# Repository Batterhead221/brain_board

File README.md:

# BRAIN_BOARD

Custom STM32H753 main controller board for modular motion, control, storage, communication, and daughter-board expansion.

BRAIN_BOARD is the clean logic/control board in a modular hardware system. It handles MCU control, communication, debugging/programming, storage, sensor inputs, and daughter-board interfaces. Noisy motor power and phase switching are kept on external boards such as DIRTY_MTR_BOARD.

## Project Status

In progress. Main controller schematic and PCB layout under development/review.

## System Role

```text
Host / USB / RS485 / CAN
        ↓
BRAIN_BOARD
        ↓ STEP / DIR / SPI / GPIO
DIRTY_MTR_BOARD / daughter boards
        ↓
Motor / sensors / external hardware
```

BRAIN_BOARD does not directly drive stepper motor coils. Motor current, switching, and noisy power handling belong on dedicated daughter boards.

## Key Specs

| Item | Value |
|---|---|
| MCU | STM32H753ZITx |
| Package | LQFP-144 |
| Logic rail | +3.3V |
| USB | USB-C |
| External communication | RS485, CAN |
| Storage | microSD |
| Nonvolatile memory | SPI FRAM |
| Debug/programming | SWD / debug UART headers |
| Daughter-board support | Motor/control, analog I/O, manual jog, external flags |
| Power options | USB or VIN path with jumper selection |
| Board role | Main controller / system brain |

## Main Features

- STM32H753 main MCU
- USB-C connector for USB data/power path
- USB VBUS fused input
- VIN input path
- Jumper-selectable power source
- +3.3V regulation and local decoupling
- RS485 transceiver interface
- CAN interface connector
- SPI FRAM
- microSD card interface
- SWD programming/debug header
- Debug UART header
- User switch
- Boot button
- Reset button
- Status LEDs
- Analog input header
- Daughter-board connectors
- Motor-control signals routed to external motor driver board
- Active-low home/crash/manual-jog style inputs
- Labeled test points and silkscreen notes

## Power Architecture

BRAIN_BOARD is intended to keep logic power clean and separate from noisy motor power.

```text
USB-C / VIN input path
        ↓
power selection / protection
        ↓
+3.3V logic rail
        ↓
STM32H753 + memory + communication interfaces
```

Motor power is not generated or switched directly on BRAIN_BOARD.

## Daughter-Board Strategy

Planned or related daughter boards include:

- DIRTY_MTR_BOARD for motor driving and noisy power handling
- DUMB_MANUAL_MTR_BOARD for external manual jog buttons
- Sensor / analog input boards
- Communication or debug helper boards

Manual jog style inputs are intended to be active-low. External buttons pull the signal to GND when pressed.

## PCB Notes

Design priorities:

- Keep MCU decoupling tight and local
- Keep the ground system solid and low impedance
- Route communication interfaces cleanly
- Keep noisy motor-driver current off the main controller board
- Use clear connector labels and test points
- Preserve clean SWD/debug access

## Repository Output Images

Expected image paths for GitHub README rendering:

```text
Outputs/
  IMG/
    3D-T.png
    3D-B.png
    SCHEMATIC.png
    L1-SIG.png
    L2-3V3.png
    L3-GND.png
    L4-MIX.png
```

## Safety / Design Note

BRAIN_BOARD is a low-voltage controller PCB. Motor power, external loads, and high-current switching should be handled on separate boards with appropriate power routing, protection, and review.

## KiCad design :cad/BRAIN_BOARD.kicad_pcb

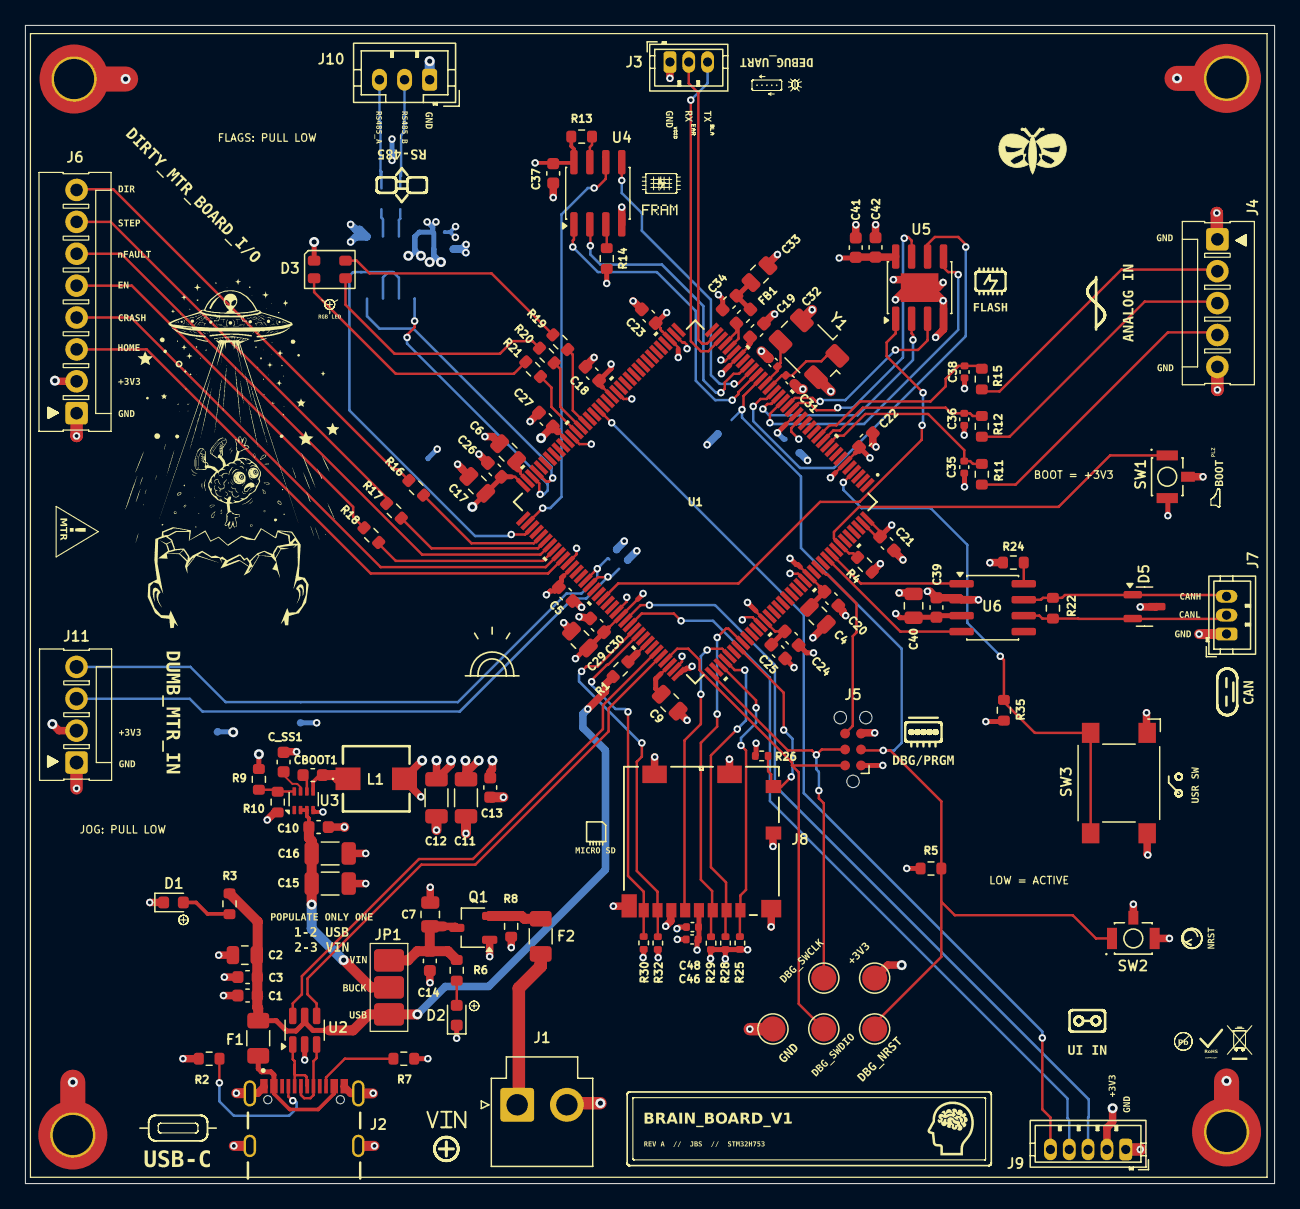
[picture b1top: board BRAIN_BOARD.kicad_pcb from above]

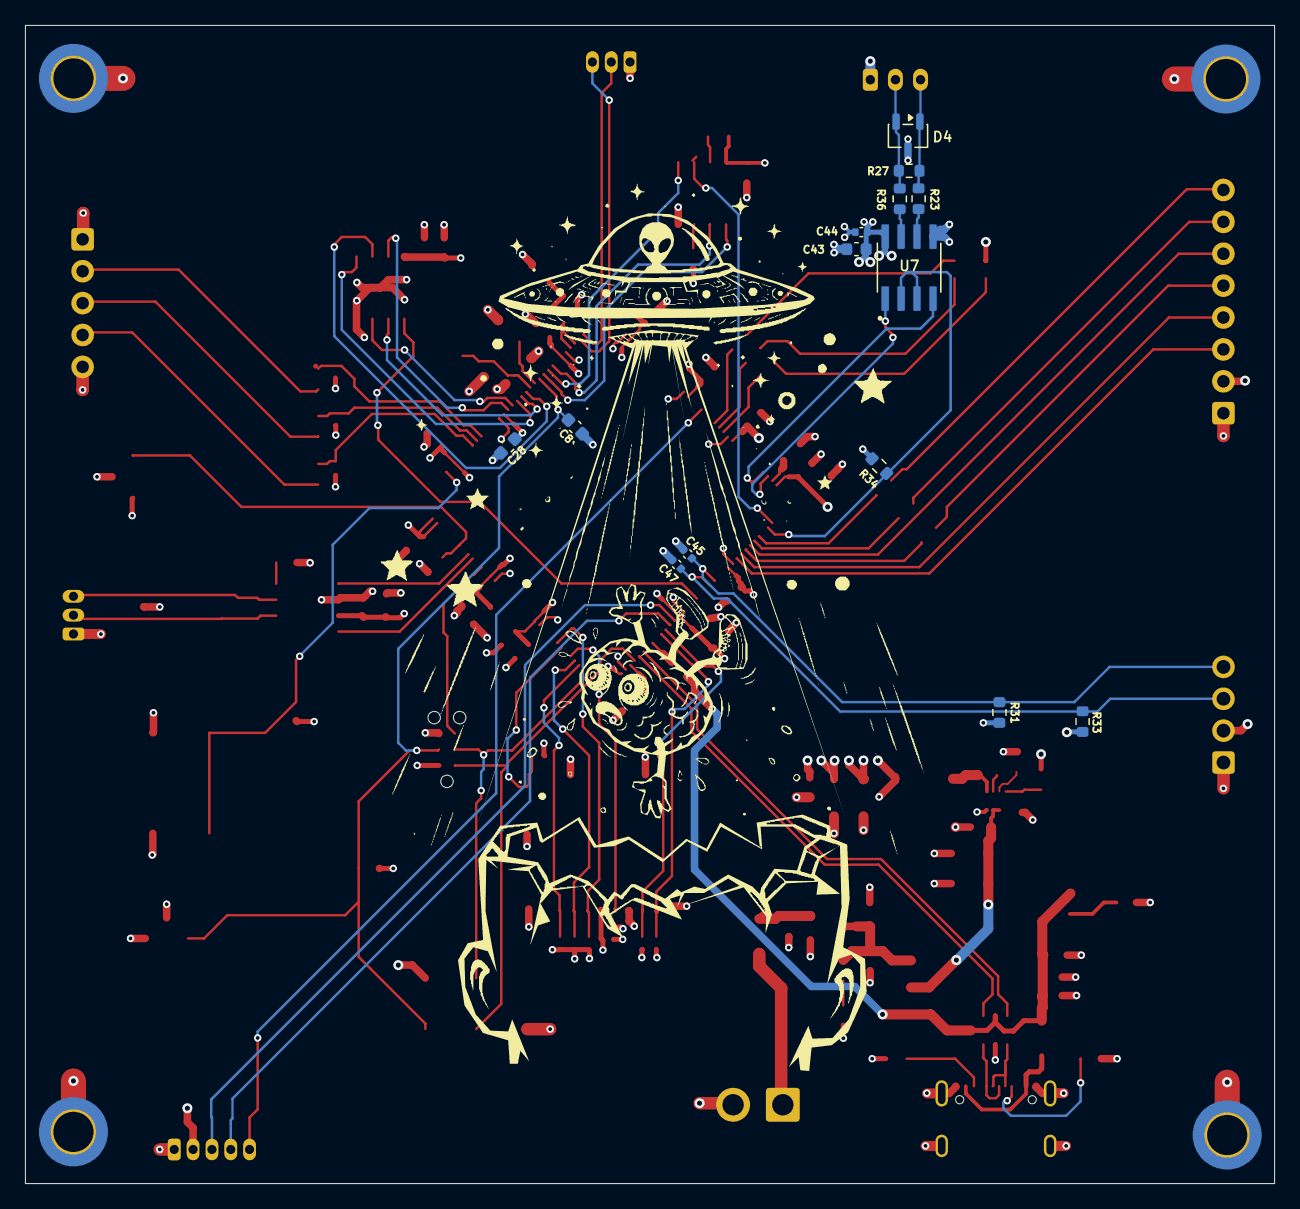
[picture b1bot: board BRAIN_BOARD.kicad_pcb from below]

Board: 4 copper layers, 99.5 x 92.2 mm, 128 parts (14 on the bottom side), 92 nets.

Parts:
C1, C5, C8, C10, C13, C14, C18, C19, C20, C21, C22, C23, C24, C25, C26, C27, C28, C30, C34, C37, C41: 100nF; C_0603_1608Metric
C2, C7: 10µF; C_0805_2012Metric
C3, C42: 1µF; C_0603_1608Metric
C4, C6, C9: 2.2µF; C_0805_2012Metric
C11, C12: 22µF; C_1206_3216Metric
C15, C16: 10µF; C_1206_3216Metric
C17, C40: 4.7µF; C_0805_2012Metric
C29, C33: 1µF; C_0805_2012Metric
C31, C32: 18pF; C_0402_1005Metric
C35, C36, C38, C45, C47: 10nF; C_0402_1005Metric
C39: 100NF; C_0603_1608Metric
C43: 10µF; C_0603_1608Metric
C44, C46: 100nF; C_0402_1005Metric
C48: 1µF; C_0402_1005Metric
CBOOT1: 100nF; C_0603_1608Metric
C_SS1: 33nF; C_0603_1608Metric
D1: +5V_SIG; LED_0603_1608Metric
D2: LED_GREEN; LED_0603_1608Metric
D3: CLV1L-FKB; LED_Cree-PLCC4_3.2x2.8mm_CCW
D4: SM712_SOT23; SOT-23-3
D5: SM24CANB-02HTG (SOT-23-3); SOT-23
F1, F2: 1206; Fuse_1206_3216Metric
FB1: FERRITE_BEAD; Fuse_0603_1608Metric
H1, H2, H3, H4: MountingHole_Pad; MountingHole_3.2mm_M3_ISO14580_Pad_TopBottom
J1: VH; JST_VH_B2P-VH_1x02_P3.96mm_Vertical
J2: USB4105-GF-A (USB-C); GCT_USB4105-GF-A
J3, J7: ZH-3; JST_ZH_B3B-ZR_1x03_P1.50mm_Vertical
J4: MTA-5
J5: TC2030-NL; Tag-Connect_TC2030-IDC-NL_2x03_P1.27mm_Vertical
J6: MTA-8
J8: 1040310811; 104031-0811_MOL
J9: ZH-5; JST_ZH_B5B-ZR_1x05_P1.50mm_Vertical
J10: PH-3; JST_PH_B3B-PH-K_1x03_P2.00mm_Vertical
J11: 640454-4; MTA-4
JP1: BEEFY_JUMPER; PWR_JMP_BEEFY
L1: 4.7µH; L_SRP5030TA4R7M
Q1: AO3407A (SOT-23-3); TSOT-23
R1, R5, R8, R10, R13, R14, R31, R33, R34, R35: 10K; R_0603
R2, R7: 5.1K; R_0603
R3, R6: 750; R_0603
R4: 5K1; R_0603
R9: 31.6K; R_0603
R11, R12, R15, R16, R17, R18: 100; R_0603
R19, R20, R21: 470; R_0603
R22, R27: 120; R_0603
R23, R36: 0; R_0603
R24: 4.7K; R_0603
R25, R28, R29, R30, R32: 47K; R_0402_1005Metric
R26: 10K; R_0402_1005Metric
SW1, SW2: B3U-1100P; SW_B3U-1100P
SW3: SW_SPST_Omron_B3FS-100xP
TP1: 3.3V; TestPoint_Pad_D2.0mm
TP2: GND; TestPoint_Pad_D2.0mm
TP3: DBG_SWDIO; TestPoint_Pad_D2.0mm
TP4: DBG_NRST; TestPoint_Pad_D2.0mm
TP5: DBG_SWCLK; TestPoint_Pad_D2.0mm
U1: LQFP-144; LQFP144-20x20mm
U2: USBLC6-2SC6_(SOT-23-6); SOT-23-6
U3: TPS62933DRLR; SOT-583-8
U4: FM25V20A-G_(SOIC-8); SOIC-8_3.9x4.9mm_P1.27mm
U5: W25Q128JVEIM_TR; SOIC-8-1EP_3.9x4.9mm_P1.27mm_EP2.29x3mm
U6: TJA1051T/3_(SOIC-8); SOIC-8_3.9x4.9mm_P1.27mm
U7: THVD1450DR; SOIC127P599X175-8N
Y1: ABM3B-8.000MHZ-B2-T; Crystal_SMD_Abracon_ABM3B-4Pin_5.0x3.2mm

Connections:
+3.3V: C4.1, C5.1, C11.2, C12.2, C13.1, C17.1, C18.1, C19.1, C20.1, C21.1, C22.1, C23.1, C24.1, C25.1, C26.1, C27.1, C28.1, C29.2, C30.2, C37.2, C39.2, C40.2, C41.2, C42.2, C43.1, C44.2, C46.1, C48.2, D3.1 (A), J5.1 (+3V3), J6.2, J8.4 (VDD), J9.2, J11.2, L1.2, R5.1, R9.2, R13.1, R14.2, R25.2, R26.1, R28.2, R29.2, R30.1, R31.1, R32.1, R33.1, R35.2, SW1.2, TP1.1, U1.6 (VBAT), U1.17 (VDD), U1.30 (VDD), U1.39 (VDD), U1.52 (VDD), U1.62 (VDD), U1.72 (VDD), U1.84 (VDD), U1.95 (VDD33USB), U1.108 (VDD), U1.121 (VDD), U1.131 (VDD), U1.143 (PDR_ON), U1.144 (VDD), U4.8 (VDD), U5.8 (VCC), U6.3 (VCC), U7.8 (VCC)
/BRAIN_BOARD/+3V3_A: FB1.2, U1.32 (VREF+), U1.33 (VDDA)
/BRAIN_BOARD/+5V_SIG: D1.2 (A), R3.2
/BRAIN_BOARD/+12V: F2.1, J1.1
/BRAIN_BOARD/+12V_SIG: D2.2 (A), R6.2
/BRAIN_BOARD/ADC_5V_SENSE: C38.1, R15.1, U1.12 (PF2)
/BRAIN_BOARD/ADC_5V_SENSE_RAW: J4.2, R15.2
/BRAIN_BOARD/ADC_24V_SENSE: C36.1, R12.1, U1.11 (PF1)
/BRAIN_BOARD/ADC_24V_SENSE_RAW: J4.3, R12.2
/BRAIN_BOARD/ADC_CURRENT_SENSE: C35.1, R11.1, U1.10 (PF0)
/BRAIN_BOARD/ADC_CURRENT_SENSE_RAW: J4.4, R11.2
/BRAIN_BOARD/BOOT0: R4.1, SW1.1, U1.138 (BOOT0)
/BRAIN_BOARD/B_LED: R19.1, U1.58 (PE7)
/BRAIN_BOARD/CAN2_RX: U1.135 (PB5), U6.4 (RXD)
/BRAIN_BOARD/CAN2_TX: U1.136 (PB6), U6.1 (TXD)
/BRAIN_BOARD/CAN_HI: D5.1 (PIN_1), J7.3, R22.1, U6.7 (CANH)
/BRAIN_BOARD/CAN_LO: D5.2 (PIN_2), J7.2, R22.2, U6.6 (CANL)
/BRAIN_BOARD/CRASH_FLAG: J6.4, U1.81 (PD12)
/BRAIN_BOARD/D+: J2.A6 (D+), J2.B6 (D+), U2.3 (L2)
/BRAIN_BOARD/D-: J2.A7 (D-), J2.B7 (D-), U2.1 (L1)
/BRAIN_BOARD/DBG_NRST: C8.2, J5.3 (NRST), R5.2, SW2.1, TP4.1, U1.25 (NRST)
/BRAIN_BOARD/DBG_SWCLK: J5.4 (SWCLK), TP5.1, U1.109 (PA14)
/BRAIN_BOARD/DBG_SWDIO: J5.2 (SWDIO), TP3.1, U1.105 (PA13)
/BRAIN_BOARD/DBG_SWO: J5.6 (SWO), U1.133 (PB3)
/BRAIN_BOARD/DIR: R16.1, U1.77 (PD8)
/BRAIN_BOARD/ENABLE: R18.1, U1.80 (PD11)
/BRAIN_BOARD/FRAM_CS: U1.26 (PC0), U4.1 (~CS)
/BRAIN_BOARD/FRAM_MISO: U1.28 (PC2_C), U4.2 (SO)
/BRAIN_BOARD/FRAM_MOSI: U1.27 (PC1), U4.5 (SI)
/BRAIN_BOARD/FRAM_SCK: U1.74 (PB13), U4.6 (SCK)
/BRAIN_BOARD/G_LED: R20.1, U1.59 (PE8)
/BRAIN_BOARD/HOME_FLAG: J6.3, U1.82 (PD13)
/BRAIN_BOARD/HSE_IN: C31.1, U1.23 (PH0-OSC_IN), Y1.1
/BRAIN_BOARD/HSE_OUT: C32.2, U1.24 (PH1-OSC_OUT), Y1.3
/BRAIN_BOARD/JOG_FWD: C45.1, J11.4, R31.2, U1.87 (PG2)
/BRAIN_BOARD/JOG_REV: C47.1, J11.3, R33.2, U1.88 (PG3)
/BRAIN_BOARD/QSPI_CLK: U1.22 (PF10), U5.6 (CLK)
/BRAIN_BOARD/QSPI_CS: U1.91 (PG6), U5.1 (~CS)
/BRAIN_BOARD/QSPI_IO0: U1.20 (PF8), U5.5 (DI_(IO0))
/BRAIN_BOARD/QSPI_IO1: U1.21 (PF9), U5.2 (DO_(IO1))
/BRAIN_BOARD/QSPI_IO2: U1.19 (PF7), U5.3 (~WP_(IO2))
/BRAIN_BOARD/QSPI_IO3: U1.18 (PF6), U5.7 (~HOLD_OR_/RESET_(IO3))
/BRAIN_BOARD/RS485_A: D4.1 (A1), J10.3, R23.2, R27.1
/BRAIN_BOARD/RS485_B: D4.2 (A2), J10.2, R27.2, R36.2
/BRAIN_BOARD/RS485_DE: R34.1, U1.75 (PB14), U7.2 (~RE), U7.3 (DE)
/BRAIN_BOARD/RS485_RX: U1.70 (PB11), U7.1 (RO)
/BRAIN_BOARD/RS485_TX: U1.69 (PB10), U7.4 (DI)
/BRAIN_BOARD/R_LED: R21.1, U1.60 (PE9)
/BRAIN_BOARD/SD_ CD: J8.10 (SW_DETECT), R26.2, U1.115 (PD1)
/BRAIN_BOARD/SD_CLK: J8.5 (CLK), U1.113 (PC12)
/BRAIN_BOARD/SD_CMD: J8.3 (CMD), R29.1, U1.116 (PD2)
/BRAIN_BOARD/SD_D0: J8.7 (DAT0), R32.2, U1.98 (PC8)
/BRAIN_BOARD/SD_D1: J8.8 (DAT1), R30.2, U1.99 (PC9)
/BRAIN_BOARD/SD_D2: J8.1 (DAT2), R25.1, U1.111 (PC10)
/BRAIN_BOARD/SD_D3: J8.2 (CD/DAT3), R28.1, U1.112 (PC11)
/BRAIN_BOARD/STEP: R17.1, U1.78 (PD9)
/BRAIN_BOARD/UART_DBG_RX: J3.2, U1.35 (PA1)
/BRAIN_BOARD/UART_DBG_TX: J3.3, U1.34 (PA0-WKUP)
/BRAIN_BOARD/UI_RST: J9.5, U1.55 (PF15)
/BRAIN_BOARD/UI_UART_RX: J9.4, U1.97 (PC7)
/BRAIN_BOARD/UI_UART_TX: J9.3, U1.96 (PC6)
/BRAIN_BOARD/USB_D+: U1.104 (PA12), U2.4 (L2)
/BRAIN_BOARD/USB_D-: U1.103 (PA11), U2.6 (L1)
/BRAIN_BOARD/USR_SW: R35.1, SW3.2, U1.4 (PE5)
/BRAIN_BOARD/VBUS_FUSED: C1.1, C2.2, C3.2, F1.2, JP1.1 (A), R1.2, R3.1, U2.5 (VP)
/BRAIN_BOARD/VBUS_RAW: F1.1, J2.A4_B9 (VBUS), J2.B4_A9 (VBUS)
/BRAIN_BOARD/VIN: C7.2, C14.2, JP1.3 (B), Q1.3 (D), R6.1
/BRAIN_BOARD/VIN_FUSED: F2.2, Q1.2 (S), R8.2
/BRAIN_BOARD/nFAULT: J6.6, U1.79 (PD10)
BUCK_IN: C10.1, C15.1, C16.1, JP1.2 (C), U3.2 (EN), U3.3 (VIN)
GND: C1.2, C2.1, C3.1, C4.2, C5.2, C6.2, C7.1, C8.1, C9.2, C10.2, C11.1, C12.1, C13.2, C14.1, C15.2, C16.2, C17.2, C18.2, C19.2, C20.2, C21.2, C22.2, C23.2, C24.2, C25.2, C26.2, C27.2, C28.2, C29.1, C30.1, C31.2, C32.1, C33.1, C34.1, C35.2, C36.2, C37.1, C38.2, C39.1, C40.1, C41.1, C42.1, C43.2, C44.1, C45.2, C46.2, C47.2, C48.1, C_SS1.1, D1.1 (K), D2.1 (K), D4.3 (common), D5.3 (PIN_3), H1.1 (1_1), H2.1 (1_1), H3.1 (1_1), H4.1 (1_1), J1.2, J2.A1_B12 (GND), J2.B1_A12 (GND), J2.SH1 (SH_GND), J2.SH2 (SH_GND1), J2.SH3 (SH_GND2), J2.SH4 (SH_GND3), J3.1, J4.1, J4.5, J5.5 (GND), J6.1, J7.1, J8.6 (GND1), J8.9 (SW_DETECT), J8.11 (GND5), J8.12 (GND4), J8.13 (GND3), J8.14 (GND2), J9.1, J10.1, J11.1, Q1.1 (G), R2.1, R4.2, R7.2, R8.1, R10.1, R24.2, R34.2, SW1.3, SW2.2, SW2.3, SW3.1, TP2.1, U1.16 (VSS), U1.31 (VSSA), U1.38 (VSS), U1.51 (VSS), U1.61 (VSS), U1.83 (VSS), U1.94 (VSS), U1.107 (VSS), U1.120 (VSS), U1.130 (VSS), U2.2 (VN), U3.4 (GND), U4.4 (VSS), U5.4 (GND), U5.9 (EP), U6.2 (GND), U7.5 (GND), Y1.2, Y1.4
unnamed: C33.2, C34.2, FB1.1
unnamed: D3.4 (BK), R19.2
unnamed: D3.3 (GK), R20.2
unnamed: D3.2 (RK), R21.2
unnamed: J2.A5 (CC1), R2.2
unnamed: J2.B5 (CC2), R7.1
unnamed: J6.5, R18.2
unnamed: J6.7, R17.2
unnamed: J6.8, R16.2
unnamed: C6.1, U1.71 (VCAP1)
unnamed: C9.1, U1.106 (VCAP2)
unnamed: CBOOT1.1, U3.6 (BST)
unnamed: R9.1, R10.2, U3.8 (FB)
unnamed: C_SS1.2, U3.7 (SS)
unnamed: CBOOT1.2, L1.1, U3.5 (SW)
unnamed: R13.2, U4.7 (~HOLD)
unnamed: R14.1, U4.3 (~WP)
unnamed: R24.1, U6.8 (S)
unnamed: R23.1, U7.6 (A)
unnamed: R36.1, U7.7 (B)
USB_VBUS: R1.1, U1.101 (PA9)

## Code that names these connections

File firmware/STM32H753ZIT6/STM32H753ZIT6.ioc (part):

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Mcu.Name=STM32H753ZITx
Mcu.Package=LQFP144
Mcu.UserName=STM32H753ZITx
PA0.Mode=Asynchronous
PA0.Signal=UART4_TX
PA1.Mode=Asynchronous
PA1.Signal=UART4_RX
PA11.GPIOParameters=GPIO_Label
PA11.GPIO_Label=USB_D-
PA11.Mode=Device_Only
PA11.Signal=USB_OTG_FS_DM
PA12.GPIOParameters=GPIO_Label
PA12.GPIO_Label=USB_D+
PA12.Mode=Device_Only
PA12.Signal=USB_OTG_FS_DP
PA13\ (JTMS/SWDIO).GPIOParameters=GPIO_Label
PA13\ (JTMS/SWDIO).GPIO_Label=DBG_SWDIO
PA13\ (JTMS/SWDIO).Mode=Serial_Wire
PA13\ (JTMS/SWDIO).Signal=DEBUG_JTMS-SWDIO
PA14\ (JTCK/SWCLK).GPIOParameters=GPIO_Label
PA14\ (JTCK/SWCLK).GPIO_Label=DBG_SWCLK
PA14\ (JTCK/SWCLK).Mode=Serial_Wire
PA14\ (JTCK/SWCLK).Signal=DEBUG_JTCK-SWCLK
PA9.GPIOParameters=GPIO_Label
PA9.GPIO_Label=VBUS
PA9.Mode=Activate_VBUS
PA9.Signal=USB_OTG_FS_VBUS
PB10.GPIOParameters=GPIO_Label
PB10.GPIO_Label=USART3_TX (485)
PB10.Mode=Asynchronous
PB10.Signal=USART3_TX
PB11.GPIOParameters=GPIO_Label
PB11.GPIO_Label=USART3_RX (485)
PB11.Mode=Asynchronous
PB11.Signal=USART3_RX
PB12.GPIOParameters=PinState,GPIO_Label
PB12.GPIO_Label=DRV_CS
PB12.PinState=GPIO_PIN_SET
PB12.Signal=GPIO_Output
PB14.GPIOParameters=GPIO_Label
PB14.GPIO_Label=RS485_DE
PB14.Signal=GPIO_Output
PB15.GPIOParameters=GPIO_Label
PB15.GPIO_Label=MTR_nSLEEP
PB15.Signal=GPIO_Output
PB3\ (JTDO/TRACESWO).GPIOParameters=GPIO_Label
PB3\ (JTDO/TRACESWO).GPIO_Label=DBG_SWO
PB3\ (JTDO/TRACESWO).Signal=DEBUG_JTDO-SWO
PB5.GPIOParameters=GPIO_Label
PB5.GPIO_Label=CAN2_RX
PB5.Mode=FDCAN_Activate
PB5.Signal=FDCAN2_RX
PB6.GPIOParameters=GPIO_Label
PB6.GPIO_Label=CAN2_TX
PB6.Mode=FDCAN_Activate
PB6.Signal=FDCAN2_TX
PC0.GPIOParameters=PinState,GPIO_Label
PC0.GPIO_Label=FRAM_CS
PC0.PinState=GPIO_PIN_SET
PC0.Signal=GPIO_Output
PC1.GPIOParameters=GPIO_Label
PC1.GPIO_Label=FRAM_MOSI
PC1.Mode=Full_Duplex_Master
PC1.Signal=SPI2_MOSI
PC10.GPIOParameters=GPIO_Label
PC10.GPIO_Label=SD_D2
PC10.Mode=SD_4_bits_Wide_bus
PC10.Signal=SDMMC1_D2
PC11.GPIOParameters=GPIO_Label
PC11.GPIO_Label=SD_D3
PC11.Mode=SD_4_bits_Wide_bus
PC11.Signal=SDMMC1_D3
PC12.GPIOParameters=GPIO_Label
PC12.GPIO_Label=SD_CLK
PC12.Mode=SD_4_bits_Wide_bus
PC12.Signal=SDMMC1_CK
PC2_C.GPIOParameters=GPIO_Label
PC2_C.GPIO_Label=FRAM_MISO
PC2_C.Mode=Full_Duplex_Master
PC2_C.Signal=SPI2_MISO
PC6.GPIOParameters=GPIO_Label
PC6.GPIO_Label=USART6_TX (UI)
PC6.Mode=Asynchronous
PC6.Signal=USART6_TX
PC7.GPIOParameters=GPIO_Label
PC7.GPIO_Label=USART6_RX (UI)
PC7.Mode=Asynchronous
PC7.Signal=USART6_RX
PC8.GPIOParameters=GPIO_Label
PC8.GPIO_Label=SD_D0_MCU
PC8.Mode=SD_4_bits_Wide_bus
PC8.Signal=SDMMC1_D0
PC9.GPIOParameters=GPIO_Label
PC9.GPIO_Label=SD_D1_MCU
PC9.Mode=SD_4_bits_Wide_bus
PC9.Signal=SDMMC1_D1
PD1.GPIOParameters=GPIO_PuPd,GPIO_Label
PD1.GPIO_Label=SD_CD
PD1.GPIO_PuPd=GPIO_PULLUP
PD1.Signal=GPIO_Input
PD10.GPIOParameters=GPIO_PuPd,GPIO_Label
PD10.GPIO_Label=nFAULT
PD10.GPIO_PuPd=GPIO_PULLUP
PD10.Signal=GPIO_Input
PD11.GPIOParameters=GPIO_Speed,PinState,GPIO_Label
PD11.GPIO_Label=ENABLE
PD11.GPIO_Speed=GPIO_SPEED_FREQ_LOW
PD11.PinState=GPIO_PIN_RESET
PD11.Signal=GPIO_Output
PD12.GPIOParameters=GPIO_PuPd,GPIO_Label,GPIO_ModeDefaultEXTI
PD12.GPIO_Label=CRASH_FLAG
PD12.GPIO_ModeDefaultEXTI=GPIO_MODE_IT_FALLING
PD12.GPIO_PuPd=GPIO_PULLUP
PD12.Signal=GPXTI12
PD13.GPIOParameters=GPIO_PuPd,GPIO_Label,GPIO_ModeDefaultEXTI
PD13.GPIO_Label=HOME_FLAG
PD13.GPIO_ModeDefaultEXTI=GPIO_MODE_IT_FALLING
PD13.GPIO_PuPd=GPIO_PULLUP
PD13.Signal=GPXTI13
PD2.GPIOParameters=GPIO_Label
PD2.GPIO_Label=SD_CMD
PD2.Mode=SD_4_bits_Wide_bus
PD2.Signal=SDMMC1_CMD
PD3.GPIOParameters=GPIO_Label
PD3.GPIO_Label=SPI_SCK
PD3.Mode=Full_Duplex_Master
PD3.Signal=SPI2_SCK
PD8.GPIOParameters=GPIO_Label
PD8.GPIO_Label=DIR
PD8.Signal=GPIO_Output
PD9.GPIOParameters=GPIO_Label
PD9.GPIO_Label=STEP
PD9.Signal=GPIO_Output
PE5.GPIOParameters=GPIO_PuPd,GPIO_Label
PE5.GPIO_Label=USR_SW
PE5.GPIO_PuPd=GPIO_PULLUP
PE5.Signal=GPIO_Input
PE7.GPIOParameters=GPIO_Label
PE7.GPIO_Label=B_LED
PE7.Signal=GPIO_Output
PE8.GPIOParameters=GPIO_Label
PE8.GPIO_Label=G_LED
PE8.Signal=GPIO_Output
PE9.GPIOParameters=GPIO_Label
PE9.GPIO_Label=R_LED
PE9.Signal=GPIO_Output
PF10.GPIOParameters=GPIO_Label
PF10.GPIO_Label=QSPI_CLK
PF10.Mode=Single Bank 1
PF10.Signal=QUADSPI_CLK
PF15.GPIOParameters=GPIO_Label
PF15.GPIO_Label=UI_RST
PF15.Signal=GPIO_Output
PF3.GPIOParameters=GPIO_Label
PF3.GPIO_Label=ADC_CURRENT_SENSE
PF3.Mode=IN5-Single-Ended
PF3.Signal=ADC3_INP5
PF4.GPIOParameters=GPIO_Label
PF4.GPIO_Label=ADC_24V_SENSE
PF4.Mode=IN9-Single-Ended
PF4.Signal=ADC3_INP9
PF5.GPIOParameters=GPIO_Label
PF5.GPIO_Label=ADC_5V_SENSE
PF5.Mode=IN4-Single-Ended
PF5.Signal=ADC3_INP4
PF6.GPIOParameters=GPIO_Label
PF6.GPIO_Label=QSPI_IO3
PF6.Mode=Single Bank 1
PF6.Signal=QUADSPI_BK1_IO3
PF7.GPIOParameters=GPIO_Label
PF7.GPIO_Label=QSPI_IO2
PF7.Mode=Single Bank 1
PF7.Signal=QUADSPI_BK1_IO2
PF8.GPIOParameters=GPIO_Label
PF8.GPIO_Label=QSPI_IO0
PF8.Mode=Single Bank 1
PF8.Signal=QUADSPI_BK1_IO0
PF9.GPIOParameters=GPIO_Label
PF9.GPIO_Label=QSPI_IO1
PF9.Mode=Single Bank 1
PF9.Signal=QUADSPI_BK1_IO1
PG2.GPIOParameters=GPIO_PuPd,GPIO_Label
PG2.GPIO_Label=JOG_FWD
PG2.GPIO_PuPd=GPIO_PULLUP
PG2.Signal=GPIO_Input
PG3.GPIOParameters=GPIO_PuPd,GPIO_Label
PG3.GPIO_Label=JOG_REV
PG3.GPIO_PuPd=GPIO_PULLUP
PG3.Signal=GPIO_Input
PG6.GPIOParameters=GPIO_Label
PG6.GPIO_Label=QSPI_CS
PG6.Mode=Single Bank 1
PG6.Signal=QUADSPI_BK1_NCS
PH0-OSC_IN\ (PH0).GPIOParameters=GPIO_Label
PH0-OSC_IN\ (PH0).GPIO_Label=HSE_IN
PH0-OSC_IN\ (PH0).Mode=HSE-External-Oscillator
PH0-OSC_IN\ (PH0).Signal=RCC_OSC_IN
PH1-OSC_OUT\ (PH1).GPIOParameters=GPIO_Label
PH1-OSC_OUT\ (PH1).GPIO_Label=HSE_OUT
PH1-OSC_OUT\ (PH1).Mode=HSE-External-Oscillator
PH1-OSC_OUT\ (PH1).Signal=RCC_OSC_OUT
RCC.SYSCLKFreq_VALUE=64000000
board=custom

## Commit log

2026-05-01 CUBEMX
2026-05-02 Update copyright owner name in LICENSE file
2026-05-03 Add initial STM32 firmware project and gitignore
2026-05-06 removed EH connectors
2026-05-13 Revised repo
2026-05-13 Added stitching vias
2026-05-23 push
2026-05-24 Rename output image folder to uppercase
